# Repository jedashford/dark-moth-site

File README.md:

# Dark Moth — R6 integrated prototype

R6 combines the confirmed **ESP32-C3 SuperMini**, power electronics and five LED
drivers on one **18-column × 24-row (A–X) isolated-pad carrier**. The case has a
left-side button, the original faceted moth, a removable front diffuser and a
battery bay sized around the user's **67 × 36 × 10 mm, 3000 mAh protected pack**.

[Inspect the complete product](index.html#explore) ·
[Build the carrier in 3D](perfboard.html?board=carrier#workbench) ·
[Exact wiring instructions](CARRIER_GUIDE.md) ·
[Print setup](print.html) ·
[Download the R6 pack](dark-moth-r6-print-pack.zip)

**Prototype status:** digital checks, source-linked models and firmware builds do
not establish a working physical product. Purchased-part fit, actual battery
lead ratings, low-voltage operation, charging, thermal behavior and optical output
need the bench checks in [the electrical plan](PRODUCT_ELECTRICAL_PLAN.md).
Current evidence is recorded in [VERIFICATION.md](VERIFICATION.md) and
[verification-summary.json](verification-summary.json).

## What changed together

- A removable carrier cassette and raised module supports replace the old
  manufactured latch PCB and separate floor-mounted modules.
- The user's UMLIFE mini USB-C charger, separate regulated 5 V/12 V converters,
  a low-voltage supervisor and low-gate-voltage MOSFETs replace the earlier power arrangement.
  **New parts are required**; use the carrier guide's exact purchasing list.
- Five identical driver groups align on rows C/G/K/O/S. The underside carries
  insulated connections; the guide identifies every solder window and hole.
- The external harness uses **BATTERY 2-pin, BUTTON 2-pin and LIGHTS 6-pin**.
  The light connector is +12 V, green, red, blue, warm white, cool white.
- The ground-contact button uses an isolated active-LOW input. R6 firmware and
  R5 button wiring are incompatible. Flash only the revision you assembled.
- The case retains the original moth and **104 × 28 × 3 mm** removable diffuser.
  A removable insert supports the smaller **42 × 25 × 10 mm** battery.

## Build in this order

1. Read the [carrier guide](CARRIER_GUIDE.md) and check the actual board, module
   markings, battery and connector sizes. The blank is nominally 47.78 × 63.02 mm;
   the user confirmed the hole count, not the measured board outline.
2. Obtain the listed replacements and assemble one board first. Use the 3D
   inspector, hole tables and underside net view together. Shared ground means
   one electrically continuous network; unrelated positive rails and LED returns
   remain separate.
3. Follow the staged, current-limited electrical bring-up before connecting the
   battery. Do not build a batch from an untested first unit.
4. Load [R6 C3 firmware](FIRMWARE_GUIDE.md). Remove the internal 5 V service shunt
   before attaching the ESP's programming USB. The separate charging port faces
   the outside; programming access is with the lid removed.
5. Print and test the [coupon](prints/coupon.stl), then follow the
   [per-part print instructions](PRINT_GUIDE.md). All STL units are millimetres;
   exported files already have their intended bed orientation.
6. Install the carrier, battery restraint, remote button, three plug pairs and
   diffuser. Check the physical wiring and clearances before closing the lid.

## Battery and connectors

The user's battery has a factory 1.25 mm connector. The selected build replaces
only that connector with the kit's two-pin XH-style plug while retaining the
factory wires, protection circuit and sealed pouch. Change one conductor at a
time and insulate its completed contact before cutting the other. Use recessed
contacts on the battery side. Measure polarity before mating; wire colors and
housing orientation do not prove polarity.

The kit marked XH2.54 is not automatically the same geometry or rating as genuine
JST XH (2.5 mm). Use matched contacts/housings from the same kit and confirm their
fit and wire range. The connector model is a nominal fit allowance. Battery and
button are both two-pin: label both mating halves and keep them in their separate
case locations. Never swap them.

## Charge with the device off

Hold the side button for two seconds until the red cue, then release to shut
both regulated rails and the controller down. Only then connect charging USB.
Leave the button alone while charging; disconnect USB before switching the
device on again. A short tap or a Bluetooth "off" command only blacks out the
LEDs and is not the complete shutdown required for charging.

The smaller charger has no implemented automatic USB lockout or system
power-sharing circuit. This is the user-selected **off-while-charging** build.
Its battery terminals B+/B− and system terminals OUT+/OUT− have distinct roles;
the complete carrier ground goes to OUT−, never across the protection path.

Use the electrical guide's supervised open-case first-charge checks. Identify
and measure the actual charge setting, cell temperature, termination and
low-voltage cutoff before enclosing a unit. No pack-temperature sensor is
connected to this generic charger. [The charger review](CHARGER_REVIEW.md)
records the supplied module and limits.

## Print and service

[PRINT_GUIDE.md](PRINT_GUIDE.md) lists supports and orientation for every part.
[cad/parts.json](cad/parts.json) is the printable inventory. The downloadable
native support projects are unsliced reference setups; choose your real printer,
material and nozzle and inspect generated support paths before printing.

The diffuser is **purchased smoked acrylic**. `diffuser.stl` is its cutting/fit
template, not a recommendation to block the light with opaque black PETG.
Remove the two front rail screws to withdraw the sheet without opening the
main electronics lid. The dark stock previously described for the older case
was only about 94.8 mm wide; confirm the actual sheet before cutting 104 mm.

Disconnect battery and charging USB before lifting the electronics cassette.
Printed supports and the insulating liner must never press exposed solder joints
against metal hardware or the battery pouch. Wires need service slack and
strain relief at the plug saddles.

## Reproduce the design

Run from `v3-button/enclosure/`, or the extracted `dark-moth-r6/` directory.
Install OpenSCAD, Blender, Bambu Studio, Arduino CLI/ESP32 core and the Python
requirements. Geometry, slicing, firmware and browser checks use local temporary
workspaces; no command below uploads firmware or sends a print job.

```sh
python tools/build_perfboard_layout.py
python tools/build_perfboard_worksheets.py
python tools/verify_r6_electronics.py
python tools/build_firmware.py
python tools/build.py
python tests/verify.py
python tests/verify_variants.py
python tests/test_printability.py
python tools/slice_check.py
python tools/build_print_project.py
python tools/build_guide.py
/Applications/Blender.app/Contents/MacOS/Blender --background --python tools/render.py
python tests/test_full_assembly.py
python tests/audit_full_assembly.py
node --test tests/test_*.mjs
python tools/package.py
python -m unittest discover -s tests -p 'test_*.py'
```

The browser test requires Playwright and Chromium; set `PLAYWRIGHT_MODULE` if
using an existing installation. The release pack includes the exact compiled
firmware source and rejects stale source hashes or missing verification.

Run `python site/serve.py --port 8000` and open
[the local website](http://localhost:8000/). The deployed site is
[Dark Moth](https://jedashford.github.io/dark-moth-site/).

Historical KiCad files and earlier latch/driver worksheets are reference inputs
only. **CARRIER_GUIDE.md, the R6 carrier data and R6 firmware define this build.**

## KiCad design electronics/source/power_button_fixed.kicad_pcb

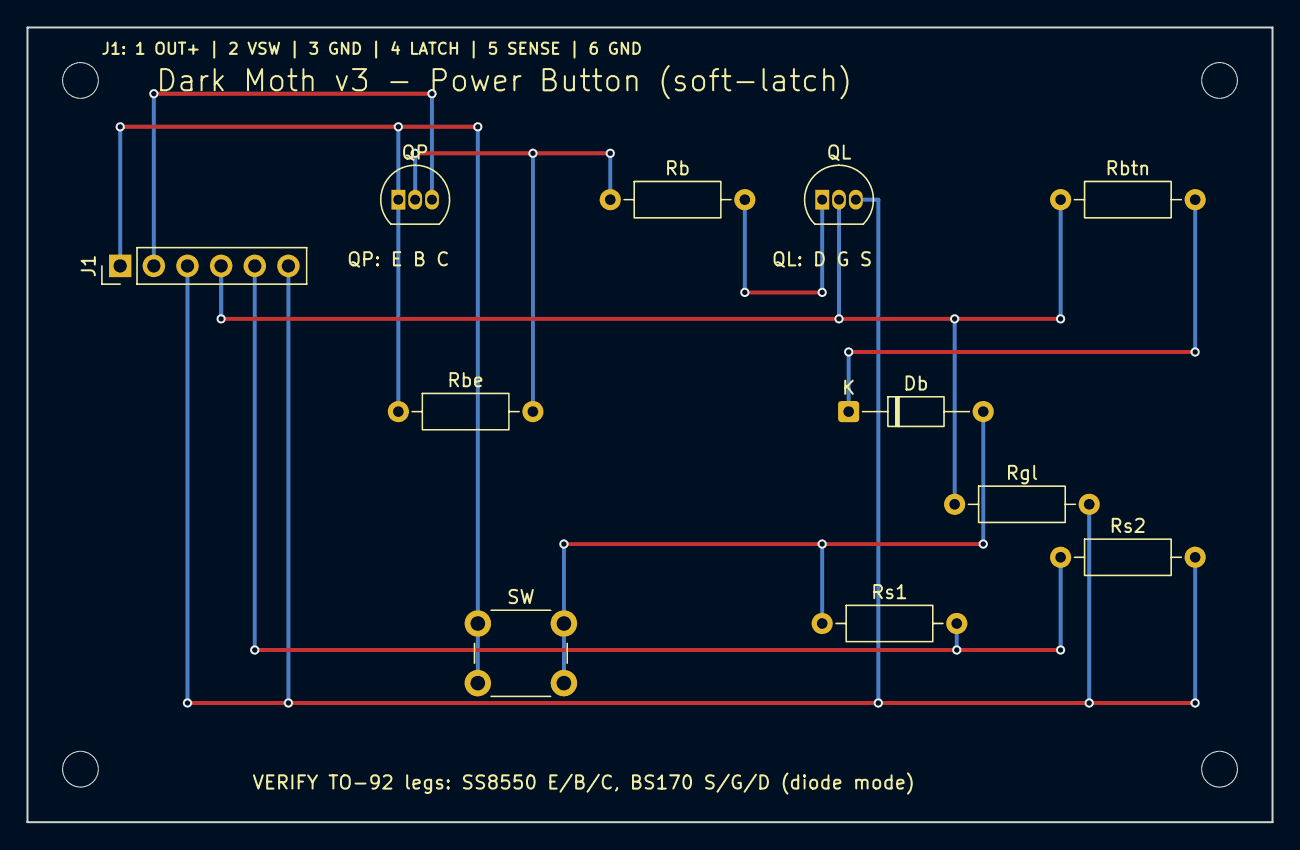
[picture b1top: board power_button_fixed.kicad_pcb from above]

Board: 2 copper layers, 94.0 x 60.0 mm, 15 parts (0 on the bottom side), 9 nets.

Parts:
Db: 1N4148; D_DO-35_SOD27_P10.16mm_Horizontal
H1, H2, H3, H4: M2.5; MountingHole_2.7mm
J1: OUT+/VSW/GND/LATCH/SENSE/GND; PinHeader_1x06_P2.54mm_Vertical
QL: BS170; TO-92_Inline
QP: SS8550; TO-92_Inline
Rb: 330; R_Axial_DIN0207_L6.3mm_D2.5mm_P10.16mm_Horizontal
Rbe: 100k; R_Axial_DIN0207_L6.3mm_D2.5mm_P10.16mm_Horizontal
Rbtn: 1k; R_Axial_DIN0207_L6.3mm_D2.5mm_P10.16mm_Horizontal
Rgl: 100k; R_Axial_DIN0207_L6.3mm_D2.5mm_P10.16mm_Horizontal
Rs1, Rs2: 100k; R_Axial_DIN0207_L6.3mm_D2.5mm_P10.16mm_Horizontal
SW: PWR; SW_PUSH_6mm

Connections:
BTN_DIO: Db.1, Rbtn.2
BTN_N: Db.2, Rs1.1, SW.1, SW.2
GATE: J1.4, QL.2, Rbtn.1, Rgl.1
GND: J1.3, J1.6, QL.3, Rgl.2, Rs2.2
LDRV: QL.1, Rb.2
OUT+: J1.1, QP.1, Rbe.1, SW.1, SW.2
PB: QP.2, Rb.1, Rbe.2
SENSE: J1.5, Rs1.2, Rs2.1
VSW: J1.2, QP.3
